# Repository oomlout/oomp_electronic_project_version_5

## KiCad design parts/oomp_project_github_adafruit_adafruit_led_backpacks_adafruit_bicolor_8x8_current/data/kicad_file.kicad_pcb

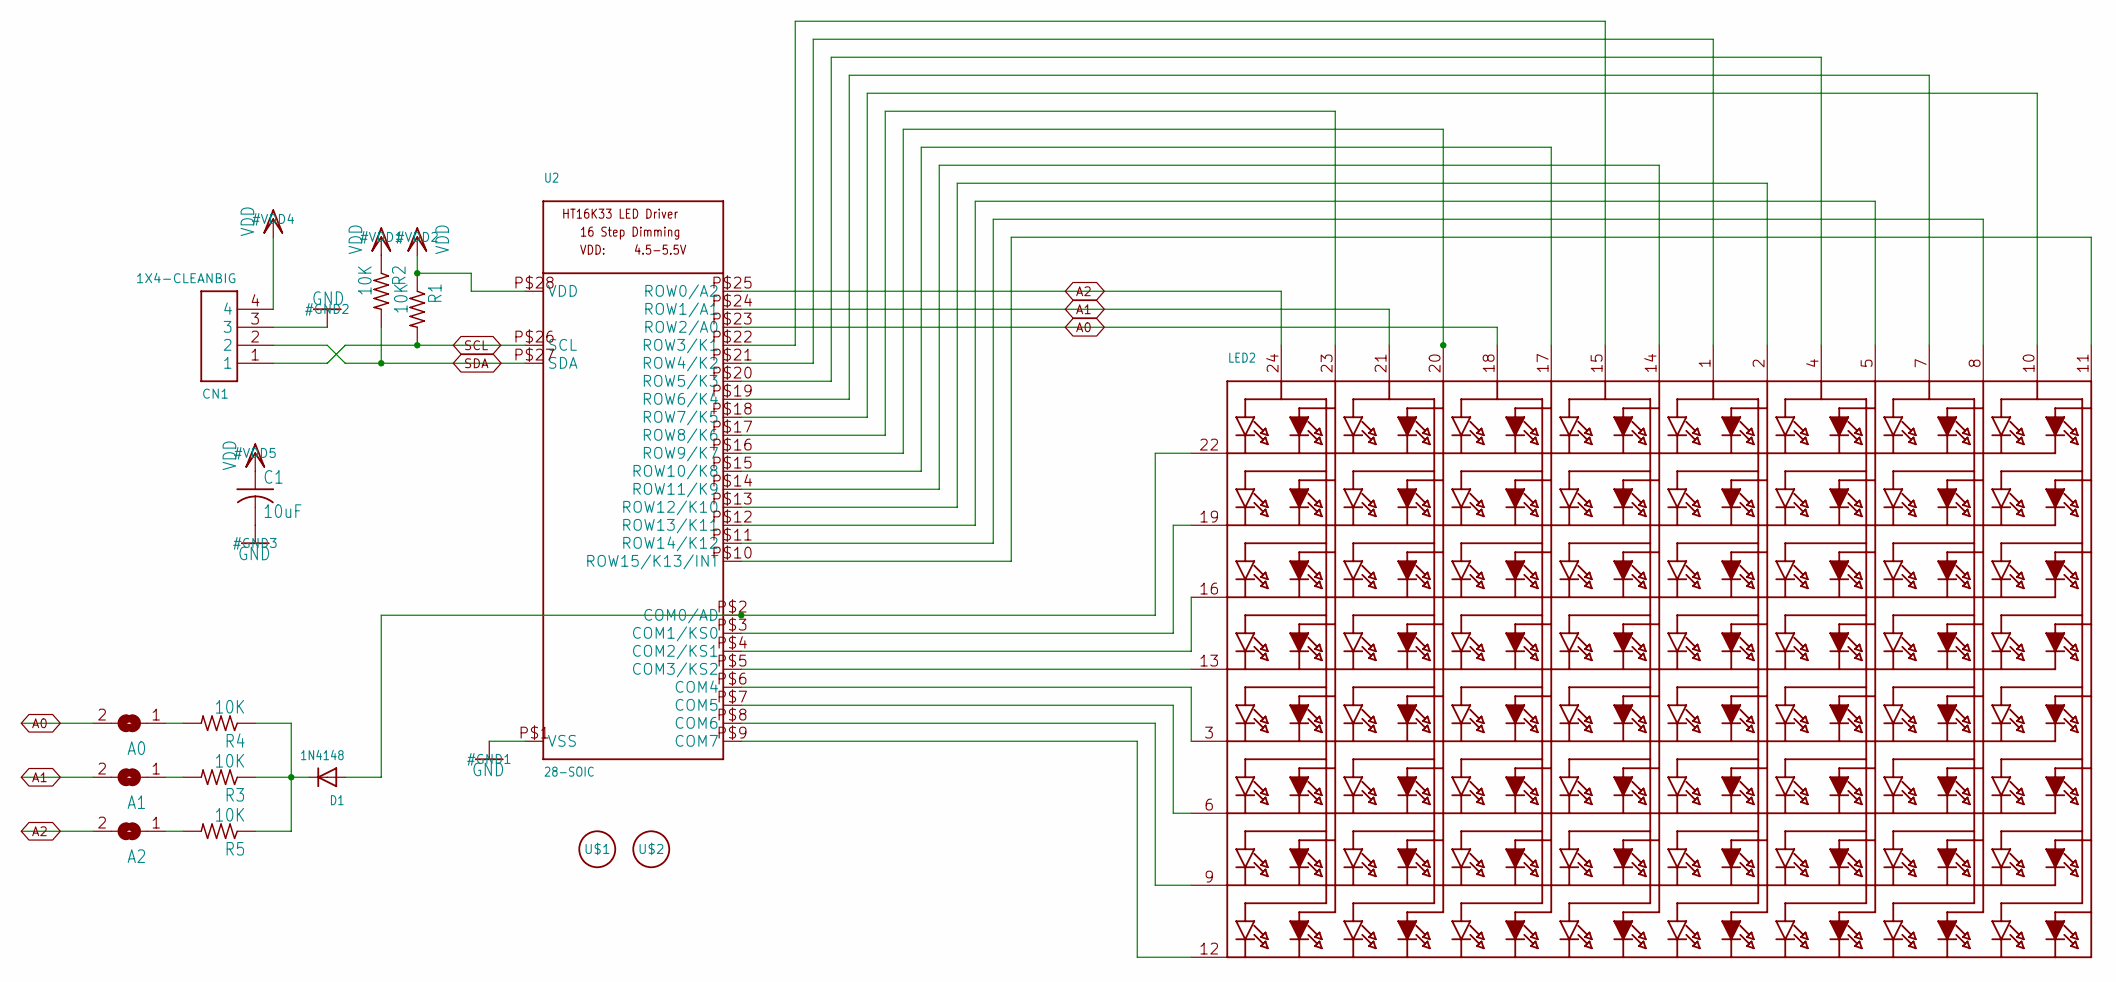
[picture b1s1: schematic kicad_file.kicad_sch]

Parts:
A0, A1, A2: SOLDERJUMPERREFLOW_NOPASTE; SOLDERJUMPER_REFLOW_NOPASTE
C1: 10uF; C0805
CN1: 1X4-CLEANBIG; 1X04-CLEANBIG
D1: 1N4148; SOD-323F
LED2: DISP_SEGMENT_8X8_BICOLOR_ROWCATHODEMI2A883XX; SEGMENT_BICOL_BL-M12A883XX
R1, R2, R3, R4, R5: 10K; R0805
U2: 28-SOIC; SOP28_300MIL
U$1, U$2: FIDUCIAL; FIDUCIAL_1MM

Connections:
A0: A0.2, LED2.18 (A5), U2.P$23 (ROW2/A0)
A1: A1.2, LED2.21 (A3), U2.P$24 (ROW1/A1)
A2: A2.2, LED2.24 (A1), U2.P$25 (ROW0/A2)
GND: C1.2, CN1.3, U2.P$1 (VSS)
unnamed: LED2.12 (K8), U2.P$9 (COM7)
unnamed: LED2.9 (K7), U2.P$8 (COM6)
unnamed: LED2.6 (K6), U2.P$7 (COM5)
unnamed: LED2.3 (K5), U2.P$6 (COM4)
unnamed: LED2.13 (K4), U2.P$5 (COM3/KS2)
unnamed: LED2.16 (K3), U2.P$4 (COM2/KS1)
unnamed: LED2.19 (K2), U2.P$3 (COM1/KS0)
unnamed: D1.A, LED2.22 (K1), U2.P$2 (COM0/AD)
unnamed: A2.1, R5.2
unnamed: LED2.8 (A14), U2.P$11 (ROW14/K12)
unnamed: LED2.5 (A12), U2.P$12 (ROW13/K11)
unnamed: LED2.11 (A16), U2.P$10 (ROW15/K13/INT)
unnamed: D1.C, R3.1, R4.1, R5.1
unnamed: A1.1, R3.2
unnamed: A0.1, R4.2
unnamed: LED2.10 (A15), U2.P$18 (ROW7/K5)
unnamed: LED2.7 (A13), U2.P$19 (ROW6/K4)
unnamed: LED2.1 (A9), U2.P$21 (ROW4/K2)
unnamed: LED2.15 (A7), U2.P$22 (ROW3/K1)
unnamed: LED2.4 (A11), U2.P$20 (ROW5/K3)
unnamed: LED2.23 (A2), U2.P$17 (ROW8/K6)
unnamed: LED2.20 (A4), U2.P$16 (ROW9/K7)
unnamed: LED2.14 (A8), U2.P$14 (ROW11/K9)
unnamed: LED2.17 (A6), U2.P$15 (ROW10/K8)
unnamed: LED2.2 (A10), U2.P$13 (ROW12/K10)
SCL: CN1.1, R1.2, U2.P$26 (SCL)
SDA: CN1.2, R2.2, U2.P$27 (SDA)
VDD: C1.1, CN1.4, R1.1, R2.1, U2.P$28 (VDD)

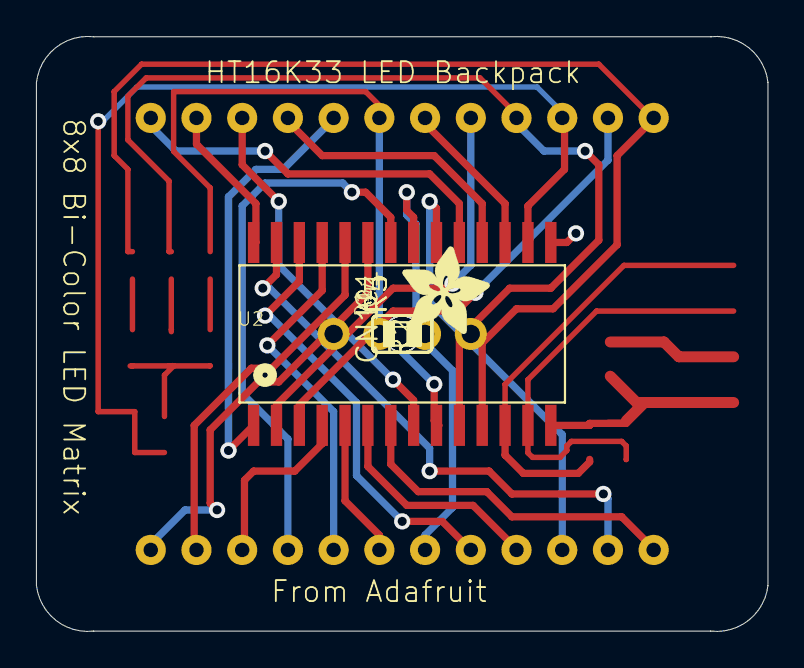
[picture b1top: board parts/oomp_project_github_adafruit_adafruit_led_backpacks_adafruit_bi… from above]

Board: 16 copper layers, 40.6 x 33.1 mm, 20 parts (1 on the bottom side), 32 nets.

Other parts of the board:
U$3: ADAFRUIT_5MM
UNK_HOLE_0: dummyfp0
UNK_HOLE_1: dummyfp1
UNK_HOLE_2: dummyfp2
UNK_HOLE_3: dummyfp3

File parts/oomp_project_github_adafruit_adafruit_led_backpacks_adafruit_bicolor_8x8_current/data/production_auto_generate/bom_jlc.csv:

Comment,Designator,Footprint,LCSC Part #
,U$3,Adafruit bicolor 8x8-import-fps:ADAFRUIT_5MM,
,LED2,Adafruit bicolor 8x8-import-fps:SEGMENT_BICOL_BL-M12A883XX,
,"A0,A1,A2",Adafruit bicolor 8x8-import-fps:SOLDERJUMPER_REFLOW_NOPASTE,
10K,"R1,R2,R3,R4,R5",Adafruit bicolor 8x8-import-fps:R0805,C17414
10uF,C1,Adafruit bicolor 8x8-import-fps:C0805,
1N4148,D1,Adafruit bicolor 8x8-import-fps:SOD-323F,
1X4-CLEANBIG,CN1,Adafruit bicolor 8x8-import-fps:1X04-CLEANBIG,
28-SOIC,U2,Adafruit bicolor 8x8-import-fps:SOP28_300MIL,
FIDUCIAL,"U$1,U$2",Adafruit bicolor 8x8-import-fps:FIDUCIAL_1MM,

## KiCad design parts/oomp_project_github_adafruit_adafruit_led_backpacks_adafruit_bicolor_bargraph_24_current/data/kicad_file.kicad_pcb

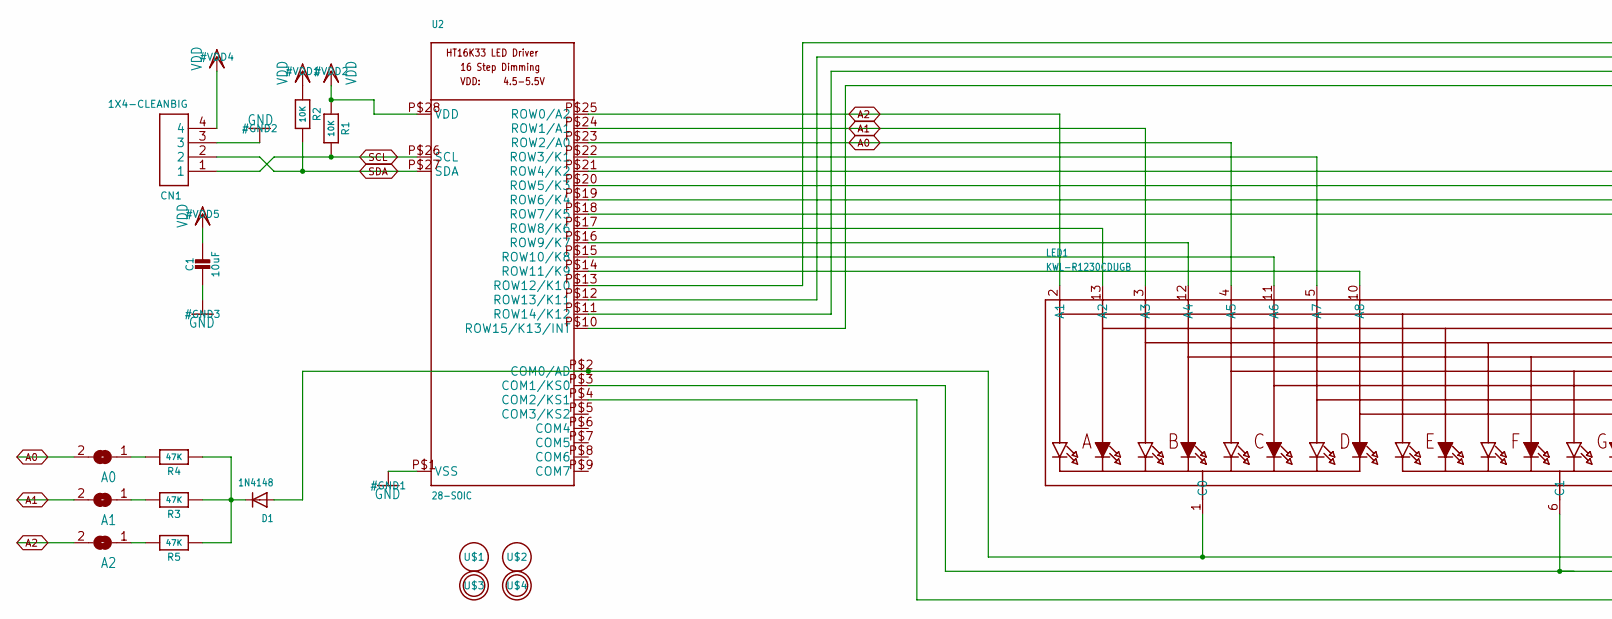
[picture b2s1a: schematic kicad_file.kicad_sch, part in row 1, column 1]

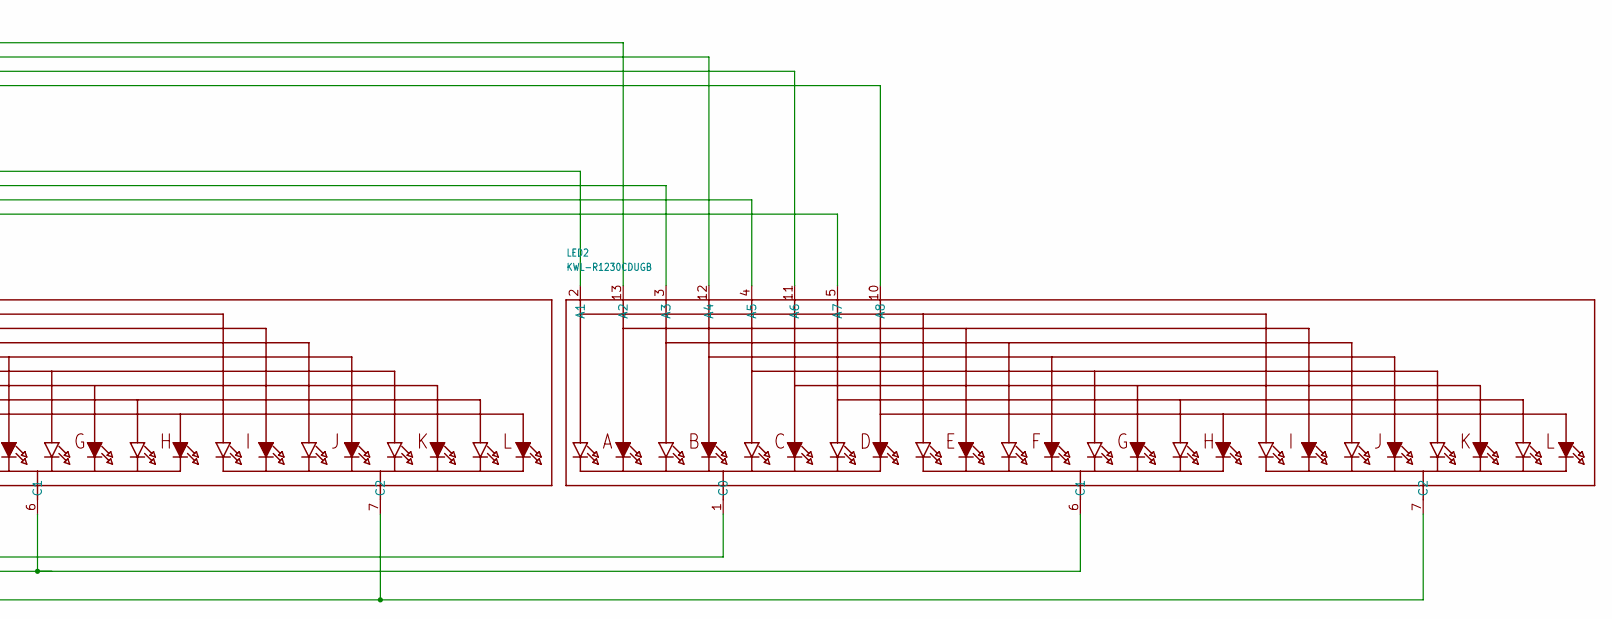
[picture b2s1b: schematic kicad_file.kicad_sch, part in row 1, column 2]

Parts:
A0, A1, A2: SOLDERJUMPERREFLOW_NOPASTE; SOLDERJUMPER_REFLOW_NOPASTE
C1: 10uF; 0805-NO
CN1: 1X4-CLEANBIG; 1X04-CLEANBIG
D1: 1N4148; SOD-323F
LED1, LED2: KWL-R1230CDUGB; SEGMENT_BICOL_BL-AR12Z3010
R1, R2: 10K; 0805-NO
R3, R4, R5: 47K; 0805-NO
U2: 28-SOIC; SOP28_300MIL
U$1, U$2: FIDUCIAL; FIDUCIAL_1MM
U$3, U$4: MOUNTINGHOLE2.5; MOUNTINGHOLE_2.5_PLATED

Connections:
A0: A0.2, LED1.4 (A5), U2.P$23 (ROW2/A0)
A1: A1.2, LED1.3 (A3), U2.P$24 (ROW1/A1)
A2: A2.2, LED1.2 (A1), U2.P$25 (ROW0/A2)
C0: D1.A, LED1.1 (C0), LED2.1 (C0), U2.P$2 (COM0/AD)
C1: LED1.6 (C1), LED2.6 (C1), U2.P$3 (COM1/KS0)
C2: LED1.7 (C2), LED2.7 (C2), U2.P$4 (COM2/KS1)
GND: C1.2, CN1.3, U2.P$1 (VSS)
unnamed: LED2.5 (A7), U2.P$18 (ROW7/K5)
unnamed: LED1.13 (A2), U2.P$17 (ROW8/K6)
unnamed: LED2.4 (A5), U2.P$19 (ROW6/K4)
unnamed: A2.1, R5.2
unnamed: D1.C, R3.1, R4.1, R5.1
unnamed: A1.1, R3.2
unnamed: A0.1, R4.2
unnamed: LED2.2 (A1), U2.P$21 (ROW4/K2)
unnamed: LED1.5 (A7), U2.P$22 (ROW3/K1)
unnamed: LED2.3 (A3), U2.P$20 (ROW5/K3)
unnamed: LED1.12 (A4), U2.P$16 (ROW9/K7)
R10: LED1.11 (A6), U2.P$15 (ROW10/K8)
R11: LED1.10 (A8), U2.P$14 (ROW11/K9)
R12: LED2.13 (A2), U2.P$13 (ROW12/K10)
R13: LED2.12 (A4), U2.P$12 (ROW13/K11)
R14: LED2.11 (A6), U2.P$11 (ROW14/K12)
R15: LED2.10 (A8), U2.P$10 (ROW15/K13/INT)
SCL: CN1.1, R1.2, U2.P$26 (SCL)
SDA: CN1.2, R2.2, U2.P$27 (SDA)
VDD: C1.1, CN1.4, R1.1, R2.1, U2.P$28 (VDD)

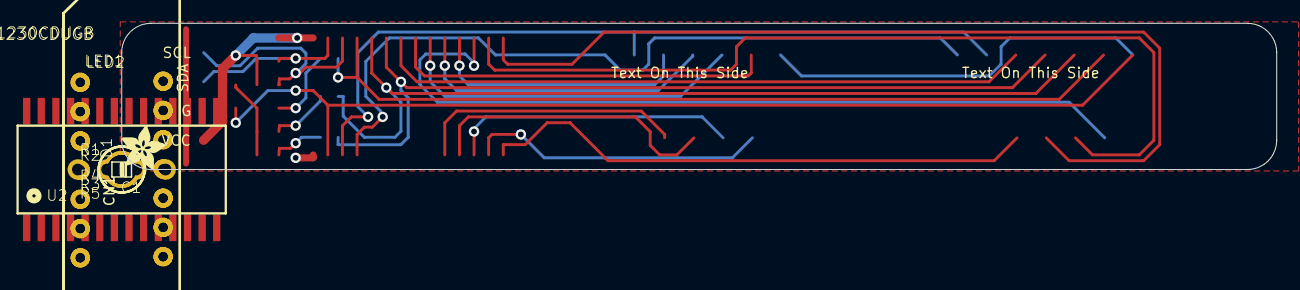
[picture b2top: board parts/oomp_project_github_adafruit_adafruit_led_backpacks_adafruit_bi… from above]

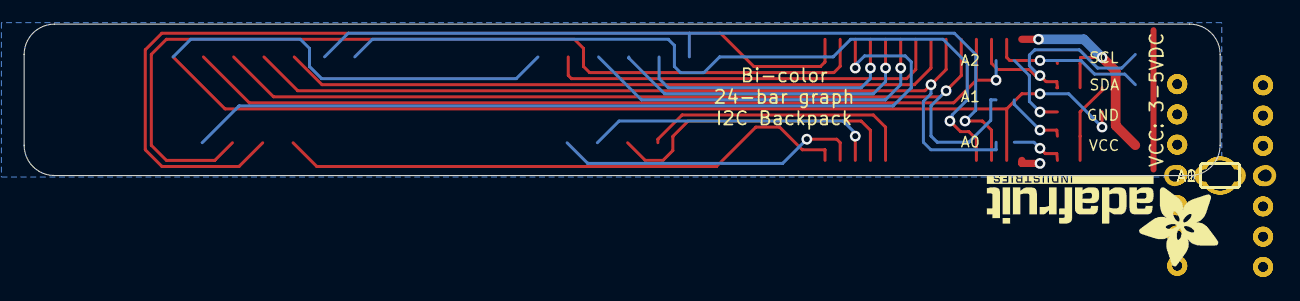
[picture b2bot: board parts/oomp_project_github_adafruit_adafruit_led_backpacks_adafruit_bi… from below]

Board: 2 copper layers, 100.3 x 12.7 mm, 20 parts (4 on the bottom side), 27 nets.

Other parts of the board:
U$5: ADAFRUIT_TEXT_20MM
U$6: ADAFRUIT_3.5MM

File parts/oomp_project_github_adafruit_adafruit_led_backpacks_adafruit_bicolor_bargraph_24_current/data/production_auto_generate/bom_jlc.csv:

Comment,Designator,Footprint,LCSC Part #
,U$6,Adafruit bicolor bargraph 24-import-fps:ADAFRUIT_3.5MM,
,U$5,Adafruit bicolor bargraph 24-import-fps:ADAFRUIT_TEXT_20MM,
,"A0,A1,A2",Adafruit bicolor bargraph 24-import-fps:SOLDERJUMPER_REFLOW_NOPASTE,
10K,"R1,R2",Adafruit bicolor bargraph 24-import-fps:0805-NO,C17414
10uF,C1,Adafruit bicolor bargraph 24-import-fps:0805-NO,
1N4148,D1,Adafruit bicolor bargraph 24-import-fps:SOD-323F,
1X4-CLEANBIG,CN1,Adafruit bicolor bargraph 24-import-fps:1X04-CLEANBIG,
28-SOIC,U2,Adafruit bicolor bargraph 24-import-fps:SOP28_300MIL,
47K,"R3,R4,R5",Adafruit bicolor bargraph 24-import-fps:0805-NO,C17713
FIDUCIAL,"U$1,U$2",Adafruit bicolor bargraph 24-import-fps:FIDUCIAL_1MM,
KWL-R1230CDUGB,"LED1,LED2",Adafruit bicolor bargraph 24-import-fps:SEGMENT_BICOL_BL-AR12Z3010,

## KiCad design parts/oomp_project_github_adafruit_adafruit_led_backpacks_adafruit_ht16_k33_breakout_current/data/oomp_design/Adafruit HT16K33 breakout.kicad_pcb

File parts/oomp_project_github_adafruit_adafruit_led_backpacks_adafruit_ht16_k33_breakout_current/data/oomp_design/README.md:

# OOMP KiCad design copy

Open `Adafruit HT16K33 breakout.kicad_pro` (or the `.kicad_pcb` / `.kicad_sch`) in KiCad. Local OOMP libraries are under `libraries/`. Original inputs are preserved in [../original/](../original/).

Only verified unchanged installed KiCad defaults were renamed. Modified, custom, unmatched and unavailable items remain unchanged. Soldering variants are never swapped during conversion. Existing pad coordinates, nets and UUIDs are preserved.

See [conversion_report.yaml](conversion_report.yaml) for every conversion and skip. Copy this directory before editing; regeneration refuses to overwrite edited design files.

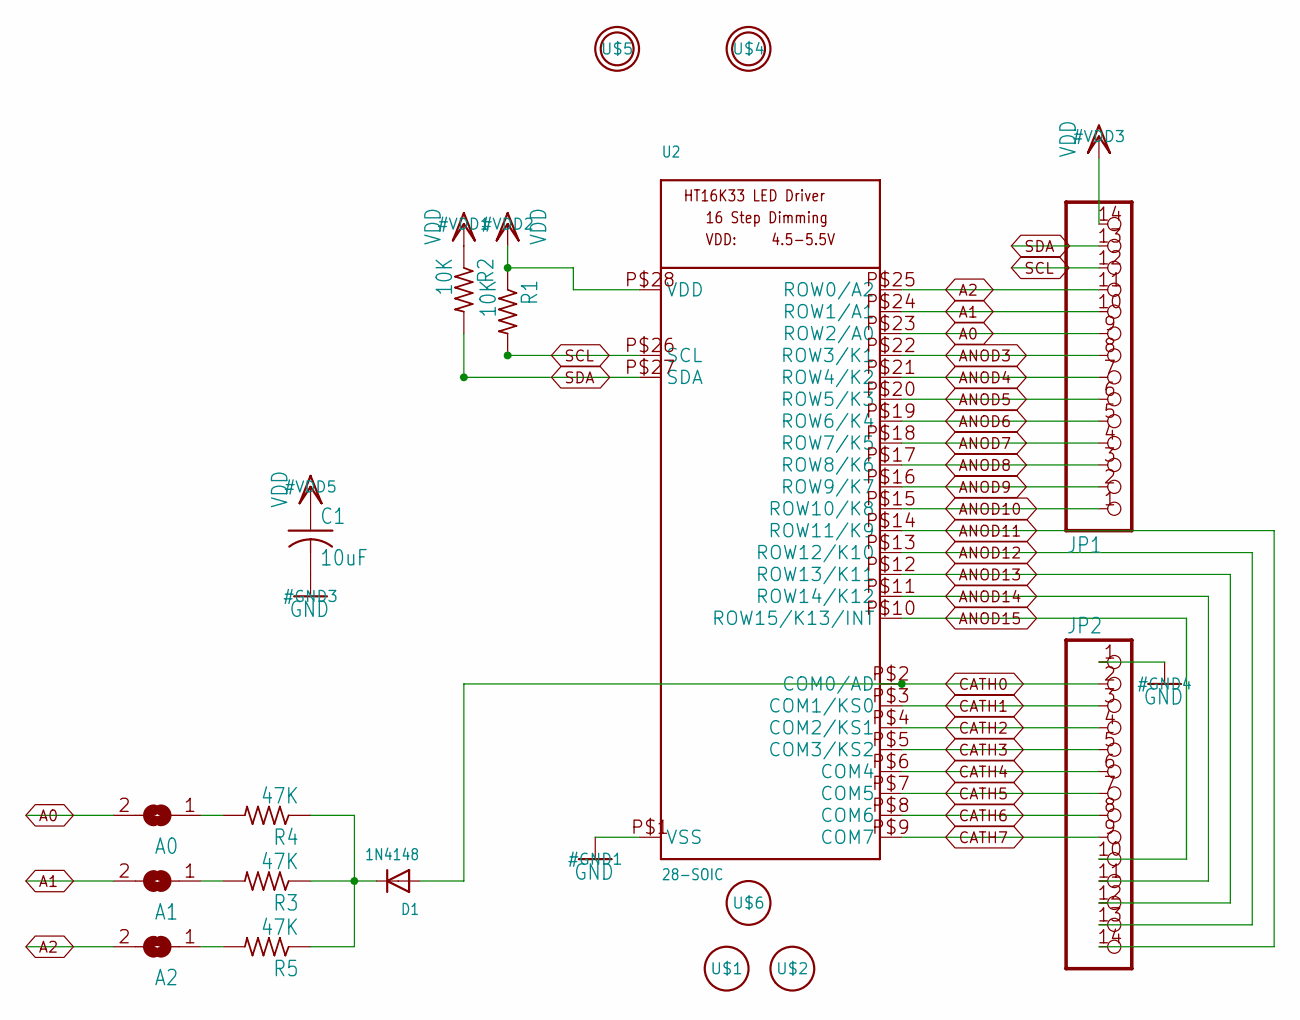
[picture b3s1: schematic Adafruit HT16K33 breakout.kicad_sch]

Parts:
A0, A1, A2: SOLDERJUMPERREFLOW_NOPASTE; SOLDERJUMPER_REFLOW_NOPASTE
C1: 10uF; C0805
D1: 1N4148; SOD-323F
JP1, JP2: PINHD-1X14-CB; 1X14-CB
R1, R2: 10K; R0805
R3, R4, R5: 47K; R0805
U2: 28-SOIC; SOP28_300MIL
U$1, U$2, U$6: FIDUCIAL; FIDUCIAL_1MM
U$4, U$5: MOUNTINGHOLE2.5; MOUNTINGHOLE_2.5_PLATED

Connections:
A0: A0.2, JP1.9, U2.P$23 (ROW2/A0)
A1: A1.2, JP1.10, U2.P$24 (ROW1/A1)
A2: A2.2, JP1.11, U2.P$25 (ROW0/A2)
ANOD3: JP1.8, U2.P$22 (ROW3/K1)
ANOD4: JP1.7, U2.P$21 (ROW4/K2)
ANOD5: JP1.6, U2.P$20 (ROW5/K3)
ANOD6: JP1.5, U2.P$19 (ROW6/K4)
ANOD7: JP1.4, U2.P$18 (ROW7/K5)
ANOD8: JP1.3, U2.P$17 (ROW8/K6)
ANOD9: JP1.2, U2.P$16 (ROW9/K7)
ANOD10: JP1.1, U2.P$15 (ROW10/K8)
ANOD11: JP2.14, U2.P$14 (ROW11/K9)
ANOD12: JP2.13, U2.P$13 (ROW12/K10)
ANOD13: JP2.12, U2.P$12 (ROW13/K11)
ANOD14: JP2.11, U2.P$11 (ROW14/K12)
ANOD15: JP2.10, U2.P$10 (ROW15/K13/INT)
CATH0: D1.A, JP2.2, U2.P$2 (COM0/AD)
CATH1: JP2.3, U2.P$3 (COM1/KS0)
CATH2: JP2.4, U2.P$4 (COM2/KS1)
CATH3: JP2.5, U2.P$5 (COM3/KS2)
CATH4: JP2.6, U2.P$6 (COM4)
CATH5: JP2.7, U2.P$7 (COM5)
CATH6: JP2.8, U2.P$8 (COM6)
CATH7: JP2.9, U2.P$9 (COM7)
GND: C1.2, JP2.1, U2.P$1 (VSS)
unnamed: A2.1, R5.2
unnamed: D1.C, R3.1, R4.1, R5.1
unnamed: A1.1, R3.2
unnamed: A0.1, R4.2
SCL: JP1.12, R1.2, U2.P$26 (SCL)
SDA: JP1.13, R2.2, U2.P$27 (SDA)
VDD: C1.1, JP1.14, R1.1, R2.1, U2.P$28 (VDD)

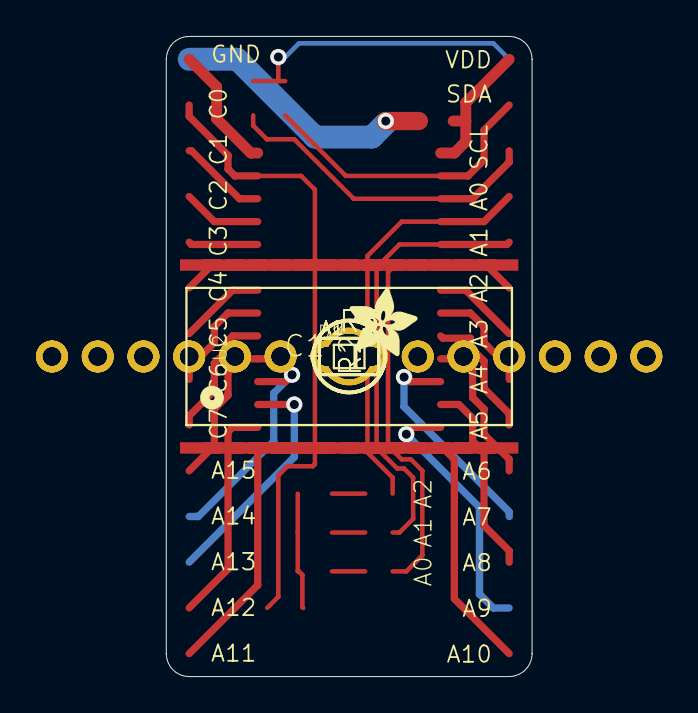
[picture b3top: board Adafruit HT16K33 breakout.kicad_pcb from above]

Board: 16 copper layers, 20.3 x 35.6 mm, 20 parts (1 on the bottom side), 32 nets.

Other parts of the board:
U$3: ADAFRUIT_3.5MM
U$7: ADAFRUIT_5MM

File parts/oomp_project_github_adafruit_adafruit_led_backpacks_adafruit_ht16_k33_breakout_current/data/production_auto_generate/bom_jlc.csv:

Comment,Designator,Footprint,LCSC Part #
,"JP1,JP2",Adafruit HT16K33 breakout-import-fps:1X14-CB,C2905490
,U$3,Adafruit HT16K33 breakout-import-fps:ADAFRUIT_3.5MM,
,U$7,Adafruit HT16K33 breakout-import-fps:ADAFRUIT_5MM,
,"A0,A1,A2",Adafruit HT16K33 breakout-import-fps:SOLDERJUMPER_REFLOW_NOPASTE,
10K,"R1,R2",Adafruit HT16K33 breakout-import-fps:R0805,C17414
10uF,C1,Adafruit HT16K33 breakout-import-fps:C0805,
1N4148,D1,Adafruit HT16K33 breakout-import-fps:SOD-323F,
28-SOIC,U2,Adafruit HT16K33 breakout-import-fps:SOP28_300MIL,
47K,"R3,R4,R5",Adafruit HT16K33 breakout-import-fps:R0805,C17713
FIDUCIAL,"U$1,U$2,U$6",Adafruit HT16K33 breakout-import-fps:FIDUCIAL_1MM,
